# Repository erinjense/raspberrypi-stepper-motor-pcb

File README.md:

# Quad Stepper Motor Driver, Printed Circuit Board

## Disclaimer

This repository, "raspberrypi-stepper-motor-pcb", includes Open Source Hardware "DESGIN FILES AND GUIDES".

THE "DESIGN FILES AND GUIDES" ARE PROVIDED “AS IS”, WITHOUT WARRANTY OF ANY KIND, EXPRESS OR IMPLIED, INCLUDING BUT NOT LIMITED TO THE WARRANTIES OF MERCHANTABILITY, FITNESS FOR A PARTICULAR PURPOSE AND NONINFRINGEMENT. IN NO EVENT SHALL THE AUTHORS OR COPYRIGHT HOLDERS BE LIABLE FOR ANY CLAIM, DAMAGES OR OTHER LIABILITY, WHETHER IN AN ACTION OF CONTRACT, TORT OR OTHERWISE, ARISING FROM, OUT OF OR IN CONNECTION WITH THE "DESIGN FILES AND GUIDES" OR THE USE OR OTHER DEALINGS IN THE "DESIGN FILES AND GUIDES".

See [LICENSE](./LICENSE.md) for further details.

NOTE: This is not a Raspberry Pi "HAT" (Hardware Attached Top). A Raspberry Pi "HAT" is a specification by the Raspberry Pi Foundation set out to ensure various modules designed to interface with the Raspberry Pi do not conflict with each other. It is up to the User to ensure that the GPIO pins within this PCB module does not conflict with other modules, "HAT"s or desired use-cases.

See more within: [Raspberry Pi HAT Details](https://github.com/raspberrypi/hats)

This device is under test and not guaranteed to operate within electrical specifications or desired functionality.

##  Device Overview

### Features
✔️ Interfaces to Raspberry Pi, single-board computer, 40W GPIO Connector.

✔️ Drives up to 4 Stepper Motors.

✔️ Step Mode Control Switches.
 - Full, 1/2, 1/4, and 1/8

✔️ Motor Drive Current Limiting Potentiometers.

✔️ Mixed Decay Mode.

✔️ Minimal Raspberry Pi GPIO Pin Usage
-  Pins: 11, 13, 15, 29, 31 

✔️ DC Barrel Jack for commonly available power supplies.

### Electrical Specifications
✔️ VM Motor Power Supply (DC barrel jack): 8 ~ 32V

✔️ Continuous Motor Output Current: 0 ~ 1.5 A / Motor Set

✔️ Working Temperature: TBD

## Guides
- [Motor Selection](#motor-selection-guide)
- [Device Operation](#device-operation-guide)
- [Ordering PCB](#jlcpcb-order-guide)

## Motor Selection Guide
Coming soon...

## Device Operation Guide
Coming soon...

## Ordering Guide
This order guide covers the following:

- Purchasing printed circuit boards from JLCPCB with SMT assembly.
- Ordering remaining, through-hole, components from LCSC.

### Step 1: Upload Gerber Files
 - Download or clone this repository onto your computer.
 - Go to [JLCPCB.com](https://jlcpcb.com/)
 - Select "Quote Now" on the right-hand of JLCPCB.

- Select "Add your gerber file" on JLCPCB.
- Locate the "gerber" directory within this repository on your computer.
- Select and upload "gerber.zip".

### Step 2: Confirm PCB Specifications
- Confirm the following optional PCB specifications:
    - PCB Qty
    - Surface Finish (Lead-Free is extra money, but I chose this option.)
- Leave remaining options default unless you have a reason to change.

### Step 3: Optional SMT Assembly
- Toggle "SMT Assembly" option.
- Select "Assemble top side".
- Select your "SMT Qty" preference. (5 vs. 2)
- Leave Tooling holes as: "Added by JLCPCB".
- Click "Confirm".

- ### Upload BOM and CPL
    - Click "Add BOM File".
    - Go to the "assembly" directory within the repository location on your computer.
    - Select "raspi-quad-stepper-motor-module_bom_jlc.csv"
    - Click "Add CPL File".
    - Go to the "assembly" directory within the repository location on your computer.
    - Select "raspi-quad-stepper-motor-module_cpl_jlc.csv"

### Step 4: Review Charge Details
- If you chose "SMT assembly" you will see the SMT devices that will be populated on the boards.

- Notice that the through-hole components will still need to be ordered and soldered by hand.

### Step 5: Purchase Remaining Components on LCSC

### Upload Through Hole BOM
- Go to [LCSC.com](https://lcsc.com/)
- Select "BOM Tool" within the LCSC banner.
- Upload BOM File by choosing "select a file" on LCSC.
- Go to the "assembly" directory within this repository on your computer.
- Select "raspi-quad-stepper-motor-module_bom_through_hole_lcsc.xlsx"

NOTE: If you did not choose SMT assembly on JLCPCB, you will have to order all the components, not just the through-hole parts, by uploading the "raspi-quad-stepper-motor-module_bom_jlc.csv" instead of "raspi-quad-stepper-motor-module_bom_through_hole_lcsc.xlsx".

### Select BOM Column Types
- Locate the "LCSC Part Number" column.
- Select "LCSC Part Number" from the above drop-down box.
- Locate the "Quantity" column.
- Select "Quantity" from the above drop-down box.
- Leave remaining columns as "select type".

### Step 6: Confirm Purchases
- Confirm your JLCPCB order.
- Confirm your LCSC order.

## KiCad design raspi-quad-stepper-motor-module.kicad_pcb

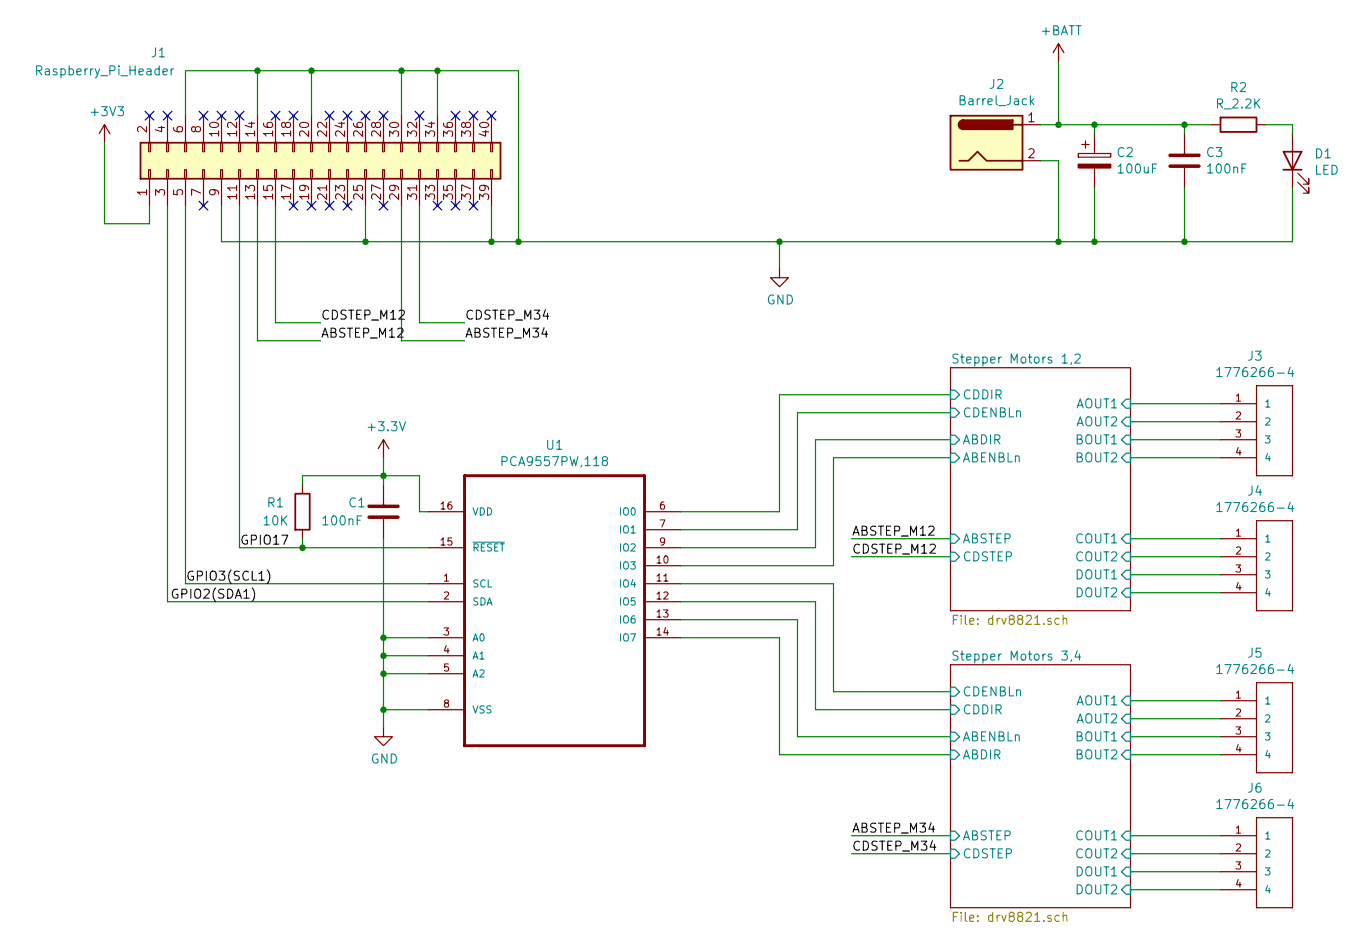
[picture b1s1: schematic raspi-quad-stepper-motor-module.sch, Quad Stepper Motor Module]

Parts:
C1, C3: 100nF; C_0805_2012Metric; LCSC C28233
C2: 100uF; CP_Elec_6.3x7.7; LCSC C249983
D1: LED; LED_1206_3216Metric; LCSC C84270
J1: Raspberry_Pi_Header; PinHeader_2x20_P2.54mm_Vertical
J2: Barrel_Jack; BarrelJack_Horizontal; LCSC C381116
J3, J4, J5, J6: 1776266-4; TE_1776266-4; LCSC C409137
R1: 10K; R_0805_2012Metric; LCSC C17414
R2: R_2.2K; R_0805_2012Metric; LCSC C17520
U1: PCA9557PW,118; SOP65P640X110-16N; LCSC C141380

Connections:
+BATT: C2.1, C3.1, J2.1, R2.2; also elsewhere on the board
/ABSTEP_M12: J1.13; also elsewhere on the board
/ABSTEP_M34: J1.29; also elsewhere on the board
/CDSTEP_M12: J1.15; also elsewhere on the board
/CDSTEP_M34: J1.31; also elsewhere on the board
/GPIO2(SDA1): J1.3, U1.2 (SDA)
/GPIO3(SCL1): J1.5, U1.1 (SCL)
/GPIO17: J1.11, R1.2, U1.15 (~RESET)
/Stepper Motors 1,2/ABDIR: U1.9 (IO2); also elsewhere on the board
/Stepper Motors 1,2/ABENBLn: U1.10 (IO3); also elsewhere on the board
/Stepper Motors 1,2/AOUT1: J3.1; also elsewhere on the board
/Stepper Motors 1,2/AOUT2: J3.2; also elsewhere on the board
/Stepper Motors 1,2/BOUT1: J3.3; also elsewhere on the board
/Stepper Motors 1,2/BOUT2: J3.4; also elsewhere on the board
/Stepper Motors 1,2/CDDIR: U1.6 (IO0); also elsewhere on the board
/Stepper Motors 1,2/CDENBLn: U1.7 (IO1); also elsewhere on the board
/Stepper Motors 1,2/COUT1: J4.1; also elsewhere on the board
/Stepper Motors 1,2/COUT2: J4.2; also elsewhere on the board
/Stepper Motors 1,2/DOUT1: J4.3; also elsewhere on the board
/Stepper Motors 1,2/DOUT2: J4.4; also elsewhere on the board
/Stepper Motors 3,4/ABDIR: U1.14 (IO7); also elsewhere on the board
/Stepper Motors 3,4/ABENBLn: U1.13 (IO6); also elsewhere on the board
/Stepper Motors 3,4/AOUT1: J5.1; also elsewhere on the board
/Stepper Motors 3,4/AOUT2: J5.2; also elsewhere on the board
/Stepper Motors 3,4/BOUT1: J5.3; also elsewhere on the board
/Stepper Motors 3,4/BOUT2: J5.4; also elsewhere on the board
/Stepper Motors 3,4/CDDIR: U1.12 (IO5); also elsewhere on the board
/Stepper Motors 3,4/CDENBLn: U1.11 (IO4); also elsewhere on the board
/Stepper Motors 3,4/COUT1: J6.1; also elsewhere on the board
/Stepper Motors 3,4/COUT2: J6.2; also elsewhere on the board
/Stepper Motors 3,4/DOUT1: J6.3; also elsewhere on the board
/Stepper Motors 3,4/DOUT2: J6.4; also elsewhere on the board
GND: C1.2, C2.2, C3.2, D1.1 (K), J1.6, J1.9, J1.14, J1.20, J1.25, J1.30, J1.34, J1.39, J2.2, U1.3 (A0), U1.4 (A1), U1.5 (A2), U1.8 (VSS); also elsewhere on the board
unnamed: D1.2 (A), R2.1

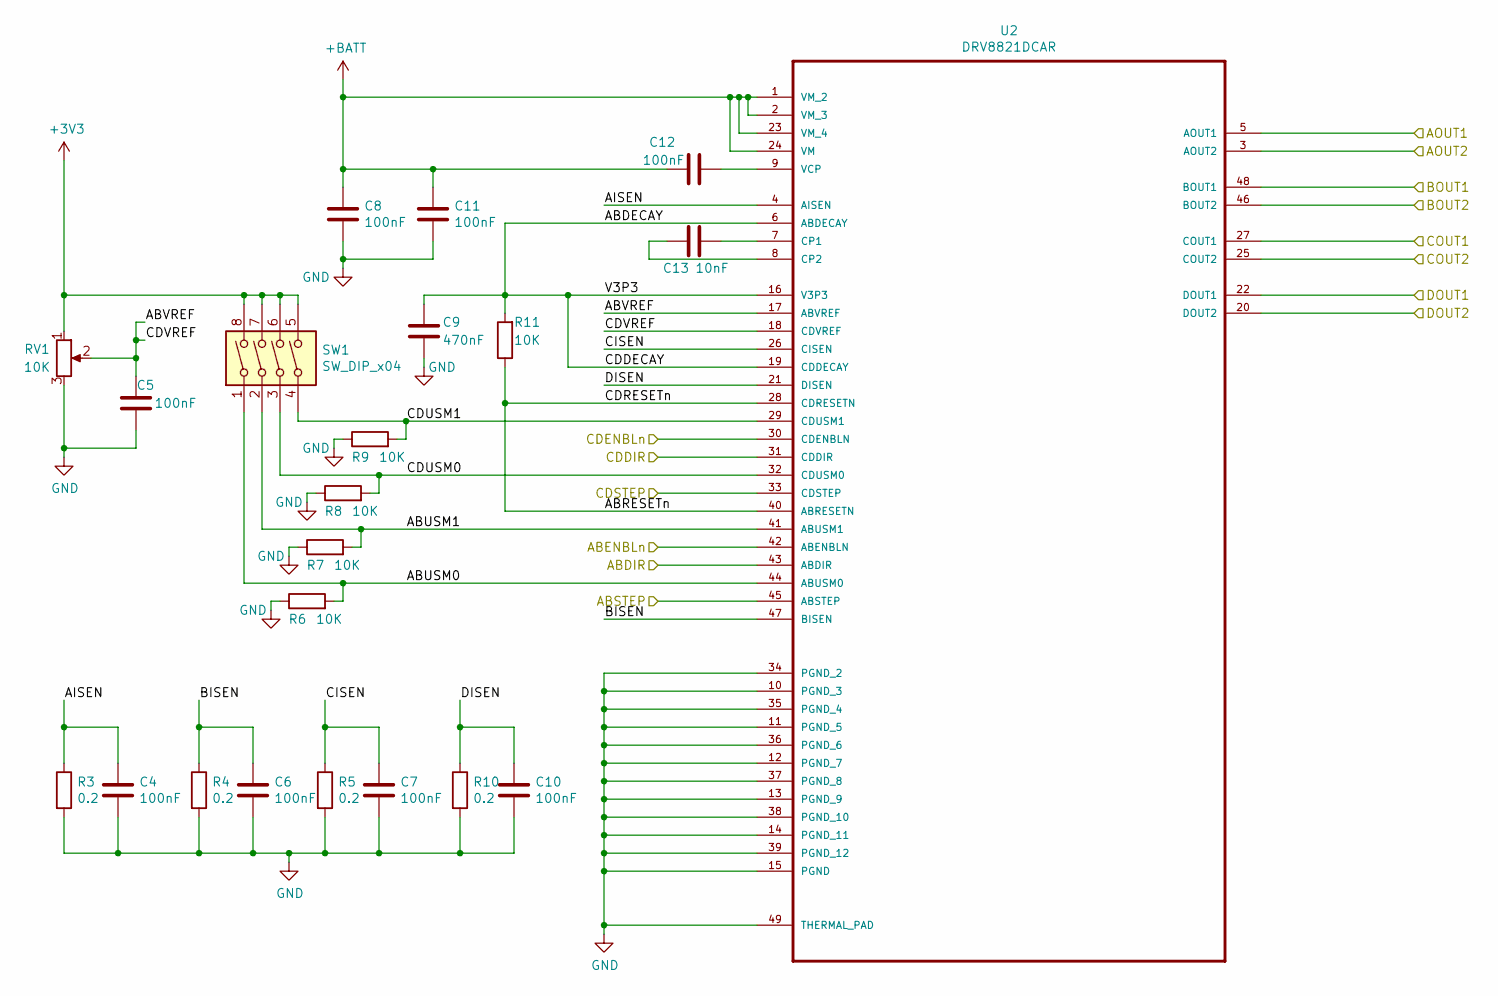
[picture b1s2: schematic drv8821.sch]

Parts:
C4, C5, C6, C7, C8, C10, C11, C12: 100nF; C_0805_2012Metric; LCSC C28233
C9: 470nF; C_0805_2012Metric; LCSC C13967
C13: 10nF; C_0805_2012Metric; LCSC C1710
R3, R4, R5, R10: 0.2; R_2512_6332Metric; LCSC C76258
R6, R7, R8, R9, R11: 10K; R_0805_2012Metric; LCSC C17414
RV1: 10K; Potentiometer_3296W_Vertical; LCSC C118954
SW1: SW_DIP_x04; SW_DIP_SPSTx04_Slide_9.78x12.34mm_W7.62mm_P2.54mm; LCSC C99418
U2: DRV8821DCAR; SOP50P810X120-49N; LCSC C81564

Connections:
+BATT: C8.1, C11.1, C12.1, U2.1 (VM_2), U2.2 (VM_3), U2.23 (VM_4), U2.24 (VM); also elsewhere on the board
/ABSTEP_M12: U2.45 (ABSTEP); also elsewhere on the board
/CDSTEP_M12: U2.33 (CDSTEP); also elsewhere on the board
/Stepper Motors 1,2/ABDECAY: C9.1, R11.2, U2.6 (ABDECAY), U2.16 (V3P3), U2.19 (CDDECAY)
/Stepper Motors 1,2/ABDIR: U2.43 (ABDIR); also elsewhere on the board
/Stepper Motors 1,2/ABENBLn: U2.42 (ABENBLN); also elsewhere on the board
/Stepper Motors 1,2/ABRESETn: R11.1, U2.28 (CDRESETN), U2.40 (ABRESETN)
/Stepper Motors 1,2/ABUSM0: R6.2, SW1.1, U2.44 (ABUSM0)
/Stepper Motors 1,2/ABUSM1: R7.2, SW1.2, U2.41 (ABUSM1)
/Stepper Motors 1,2/ABVREF: C5.1, RV1.2, U2.17 (ABVREF), U2.18 (CDVREF)
/Stepper Motors 1,2/AISEN: C4.1, R3.1, U2.4 (AISEN)
/Stepper Motors 1,2/AOUT1: U2.5 (AOUT1); also elsewhere on the board
/Stepper Motors 1,2/AOUT2: U2.3 (AOUT2); also elsewhere on the board
/Stepper Motors 1,2/BISEN: C6.1, R4.1, U2.47 (BISEN)
/Stepper Motors 1,2/BOUT1: U2.48 (BOUT1); also elsewhere on the board
/Stepper Motors 1,2/BOUT2: U2.46 (BOUT2); also elsewhere on the board
/Stepper Motors 1,2/CDDIR: U2.31 (CDDIR); also elsewhere on the board
/Stepper Motors 1,2/CDENBLn: U2.30 (CDENBLN); also elsewhere on the board
/Stepper Motors 1,2/CDUSM0: R8.2, SW1.3, U2.32 (CDUSM0)
/Stepper Motors 1,2/CDUSM1: R9.2, SW1.4, U2.29 (CDUSM1)
/Stepper Motors 1,2/CISEN: C7.1, R5.1, U2.26 (CISEN)
/Stepper Motors 1,2/COUT1: U2.27 (COUT1); also elsewhere on the board
/Stepper Motors 1,2/COUT2: U2.25 (COUT2); also elsewhere on the board
/Stepper Motors 1,2/DISEN: C10.1, R10.1, U2.21 (DISEN)
/Stepper Motors 1,2/DOUT1: U2.22 (DOUT1); also elsewhere on the board
/Stepper Motors 1,2/DOUT2: U2.20 (DOUT2); also elsewhere on the board
GND: C4.2, C5.2, C6.2, C7.2, C8.2, C9.2, C10.2, C11.2, R3.2, R4.2, R5.2, R6.1, R7.1, R8.1, R9.1, R10.2, RV1.3, U2.10 (PGND_3), U2.11 (PGND_5), U2.12 (PGND_7), U2.13 (PGND_9), U2.14 (PGND_11), U2.15 (PGND), U2.34 (PGND_2), U2.35 (PGND_4), U2.36 (PGND_6), U2.37 (PGND_8), U2.38 (PGND_10), U2.39 (PGND_12), U2.49 (THERMAL_PAD); also elsewhere on the board
unnamed: C12.2, U2.9 (VCP)
unnamed: C13.1, U2.7 (CP1)
unnamed: C13.2, U2.8 (CP2)

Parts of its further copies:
C14, C15, C16, C17, C18, C20, C21, C22: 100nF; C_0805_2012Metric; LCSC C28233
C19: 470nF; C_0805_2012Metric; LCSC C13967
C23: 10nF; C_0805_2012Metric; LCSC C1710
R12, R13, R14, R19: 0.2; R_2512_6332Metric; LCSC C76258
R15, R16, R17, R18, R20: 10K; R_0805_2012Metric; LCSC C17414
RV2: 10K; Potentiometer_3296W_Vertical; LCSC C118954
SW2: SW_DIP_x04; SW_DIP_SPSTx04_Slide_9.78x12.34mm_W7.62mm_P2.54mm; LCSC C99418
U3: DRV8821DCAR; SOP50P810X120-49N; LCSC C81564

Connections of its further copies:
+BATT: C18.1, C21.1, C22.1, U3.1 (VM_2), U3.2 (VM_3), U3.23 (VM_4), U3.24 (VM); also elsewhere on the board
/ABSTEP_M34: U3.45 (ABSTEP); also elsewhere on the board
/CDSTEP_M34: U3.33 (CDSTEP); also elsewhere on the board
/Stepper Motors 3,4/ABDECAY: C19.1, R20.2, U3.6 (ABDECAY), U3.16 (V3P3), U3.19 (CDDECAY)
/Stepper Motors 3,4/ABDIR: U3.43 (ABDIR); also elsewhere on the board
/Stepper Motors 3,4/ABENBLn: U3.42 (ABENBLN); also elsewhere on the board
/Stepper Motors 3,4/ABRESETn: R20.1, U3.28 (CDRESETN), U3.40 (ABRESETN)
/Stepper Motors 3,4/ABUSM0: R15.2, SW2.1, U3.44 (ABUSM0)
/Stepper Motors 3,4/ABUSM1: R16.2, SW2.2, U3.41 (ABUSM1)
/Stepper Motors 3,4/ABVREF: C15.1, RV2.2, U3.17 (ABVREF), U3.18 (CDVREF)
/Stepper Motors 3,4/AISEN: C14.1, R12.1, U3.4 (AISEN)
/Stepper Motors 3,4/AOUT1: U3.5 (AOUT1); also elsewhere on the board
/Stepper Motors 3,4/AOUT2: U3.3 (AOUT2); also elsewhere on the board
/Stepper Motors 3,4/BISEN: C16.1, R13.1, U3.47 (BISEN)
/Stepper Motors 3,4/BOUT1: U3.48 (BOUT1); also elsewhere on the board
/Stepper Motors 3,4/BOUT2: U3.46 (BOUT2); also elsewhere on the board
/Stepper Motors 3,4/CDDIR: U3.31 (CDDIR); also elsewhere on the board
/Stepper Motors 3,4/CDENBLn: U3.30 (CDENBLN); also elsewhere on the board
/Stepper Motors 3,4/CDUSM0: R17.2, SW2.3, U3.32 (CDUSM0)
/Stepper Motors 3,4/CDUSM1: R18.2, SW2.4, U3.29 (CDUSM1)
/Stepper Motors 3,4/CISEN: C17.1, R14.1, U3.26 (CISEN)
/Stepper Motors 3,4/COUT1: U3.27 (COUT1); also elsewhere on the board
/Stepper Motors 3,4/COUT2: U3.25 (COUT2); also elsewhere on the board
/Stepper Motors 3,4/DISEN: C20.1, R19.1, U3.21 (DISEN)
/Stepper Motors 3,4/DOUT1: U3.22 (DOUT1); also elsewhere on the board
/Stepper Motors 3,4/DOUT2: U3.20 (DOUT2); also elsewhere on the board
GND: C14.2, C15.2, C16.2, C17.2, C18.2, C19.2, C20.2, C21.2, R12.2, R13.2, R14.2, R15.1, R16.1, R17.1, R18.1, R19.2, RV2.3, U3.10 (PGND_3), U3.11 (PGND_5), U3.12 (PGND_7), U3.13 (PGND_9), U3.14 (PGND_11), U3.15 (PGND), U3.34 (PGND_2), U3.35 (PGND_4), U3.36 (PGND_6), U3.37 (PGND_8), U3.38 (PGND_10), U3.39 (PGND_12), U3.49 (THERMAL_PAD); also elsewhere on the board
unnamed: C22.2, U3.9 (VCP)
unnamed: C23.1, U3.7 (CP1)
unnamed: C23.2, U3.8 (CP2)

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
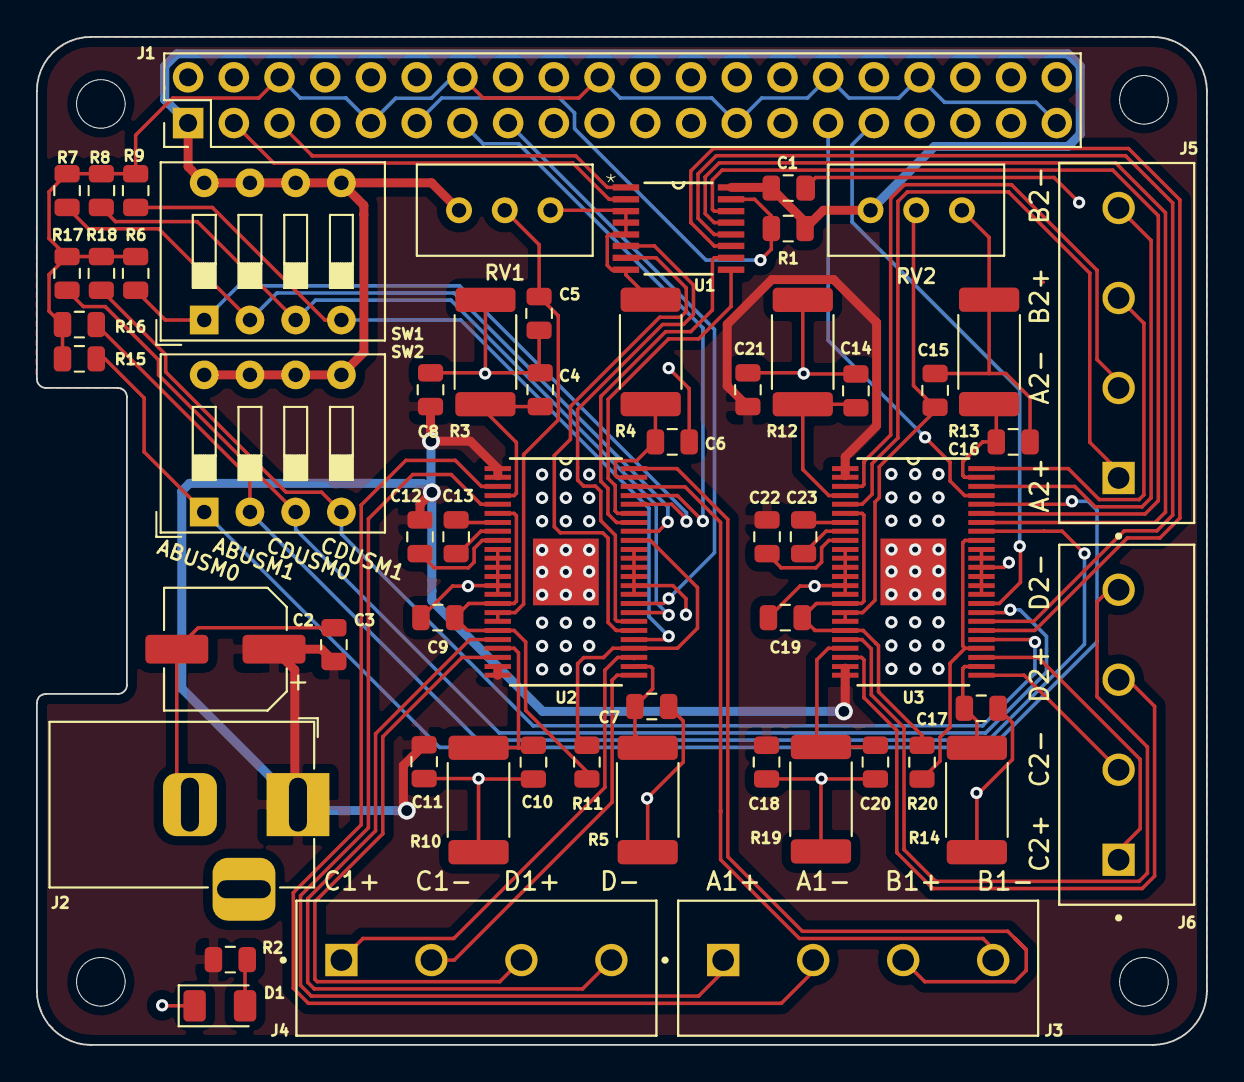
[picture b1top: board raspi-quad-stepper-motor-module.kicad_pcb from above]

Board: 2 copper layers, 65.0 x 56.0 mm, 61 parts (0 on the bottom side), 63 nets.

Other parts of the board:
MK1, MK2, MK3, MK4: M2.5; MountingHole_2.7mm_M2.5

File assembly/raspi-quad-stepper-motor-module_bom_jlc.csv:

"Comment","Designator","Footprint","LCSC Part #"
"100nF","C1,C4,C6,C7,C10,C5,C8,C11,C12,C14,C16,C17,C20,C15,C18,C21,C22","C_0805_2012Metric","C28233"
"100uF","C2","CP_Elec_6.3x7.7","C249983"
"100nF","C3","C_0805_2012Metric","C28233"
"470nF","C9,C19","C_0805_2012Metric","C13967"
"10nF","C13,C23","C_0805_2012Metric","C1710"
"LED","D1","LED_1206_3216Metric","C84270"
"Barrel_Jack","J2","BarrelJack_Horizontal","C381116"
"1776266-4","J5,J6,J3,J4","TE_1776266-4","C409137"
"10K","R1,R9,R8,R7,R6,R11,R18,R17,R16,R15,R20","R_0805_2012Metric","C17414"
"R_2.2K","R2","R_0805_2012Metric","C17520"
"0.2","R3,R4,R5,R10,R12,R13,R14,R19","R_2512_6332Metric","C76258"
"10K","RV1,RV2","Potentiometer_3296W_Vertical","C118954"
"SW_DIP_x04","SW1,SW2","SW_DIP_SPSTx04_Slide_9.78x12.34mm_W7.62mm_P2.54mm","C99418"
"PCA9557PW,118","U1","SOP65P640X110-16N","C141380"
"DRV8821DCAR","U2,U3","SOP50P810X120-49N","C81564"

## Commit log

2020-10-09 Initial Commit
    Revision A.
2020-10-09 Updated README and LICENSE.
    Added Order Guide and updated usage disclaimer.
2020-10-09 Remove duplicate images.
2020-10-09 Update README
    Update images.
